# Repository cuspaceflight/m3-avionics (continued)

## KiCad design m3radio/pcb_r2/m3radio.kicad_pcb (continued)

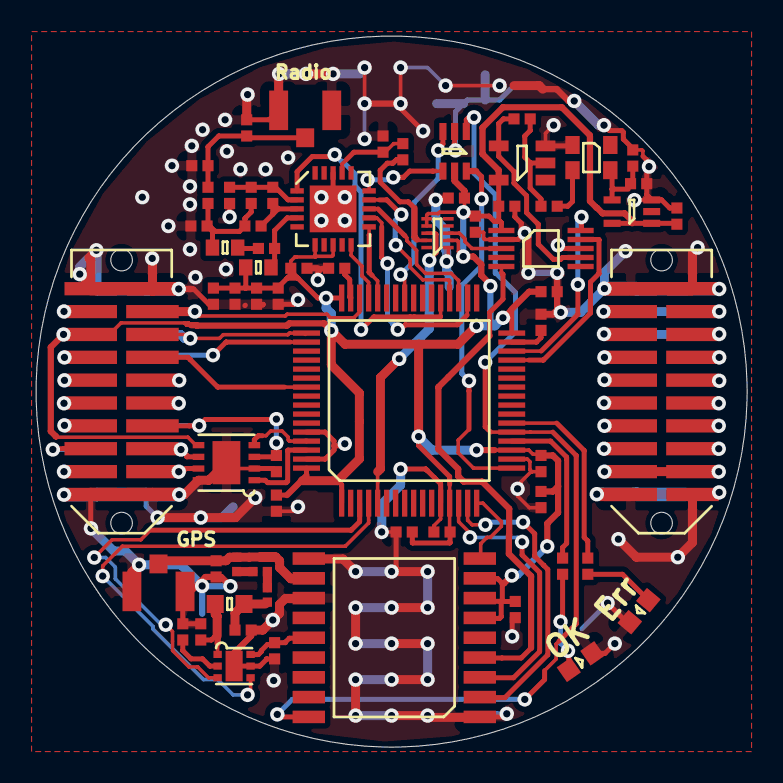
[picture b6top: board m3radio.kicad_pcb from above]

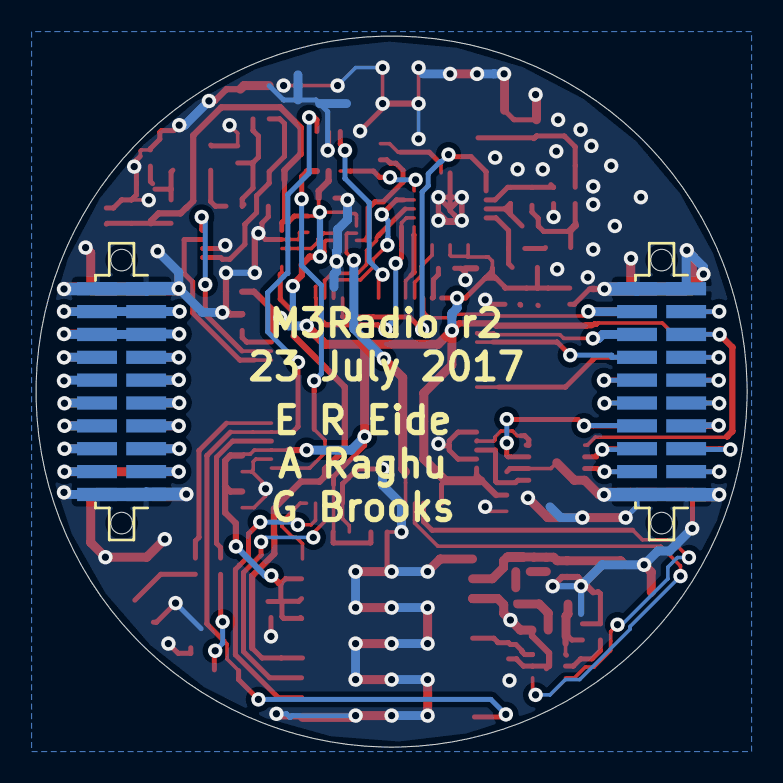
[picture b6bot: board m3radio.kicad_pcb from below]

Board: 2 copper layers, 39.5 x 39.5 mm, 66 parts (2 on the bottom side), 78 nets.

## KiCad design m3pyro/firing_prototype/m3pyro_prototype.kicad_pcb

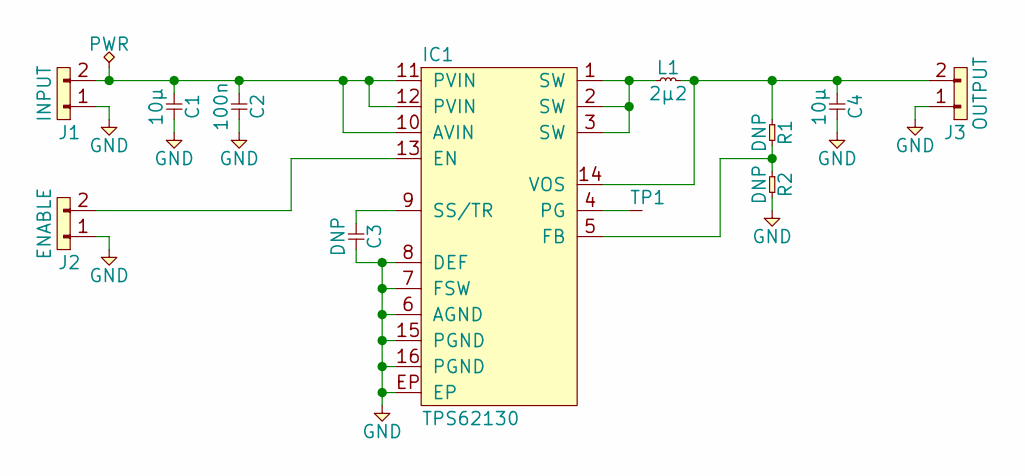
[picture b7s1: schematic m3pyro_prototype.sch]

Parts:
C1, C4: 10µ; 0603
C2: 100n; 0603
C3: DNP; 0603
IC1: TPS62130; QFN-16-EP-TI; Farnell 2361246
J1: INPUT; SIL-254P-02
J2: ENABLE; SIL-254P-02
J3: OUTPUT; SIL-254P-02
L1: 2µ2; XFL4020; Farnell 2289216
R1, R2: DNP; 0603
TP1: TESTPAD

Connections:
GND: C1.2, C2.2, C3.2, C4.2, IC1.6 (AGND), IC1.7 (FSW), IC1.8 (DEF), IC1.15 (PGND), IC1.16 (PGND), IC1.EP, J1.1, J2.1, J3.1, R2.2
unnamed: C1.1, C2.1, IC1.10 (AVIN), IC1.11 (PVIN), IC1.12 (PVIN), J1.2
unnamed: C3.1, IC1.9 (SS/TR)
unnamed: C4.1, IC1.14 (VOS), J3.2, L1.2, R1.1
unnamed: IC1.1 (SW), IC1.2 (SW), IC1.3 (SW), L1.1
unnamed: IC1.4 (PG), TP1.1
unnamed: IC1.5 (FB), R1.2, R2.1
unnamed: IC1.13 (EN), J2.2

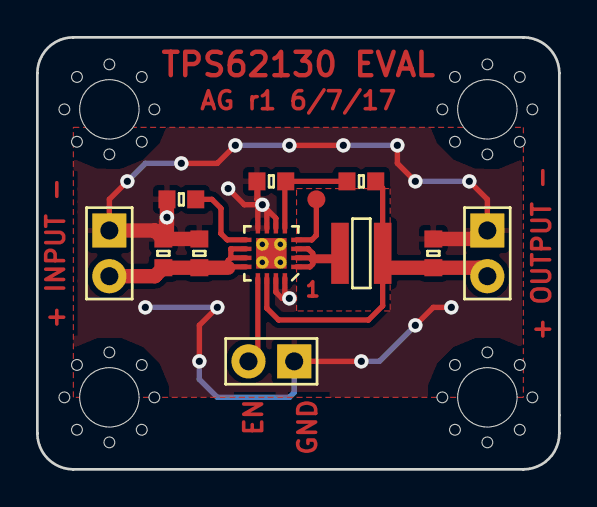
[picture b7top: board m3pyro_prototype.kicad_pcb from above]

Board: 2 copper layers, 29.0 x 24.0 mm, 12 parts (0 on the bottom side), 8 nets.

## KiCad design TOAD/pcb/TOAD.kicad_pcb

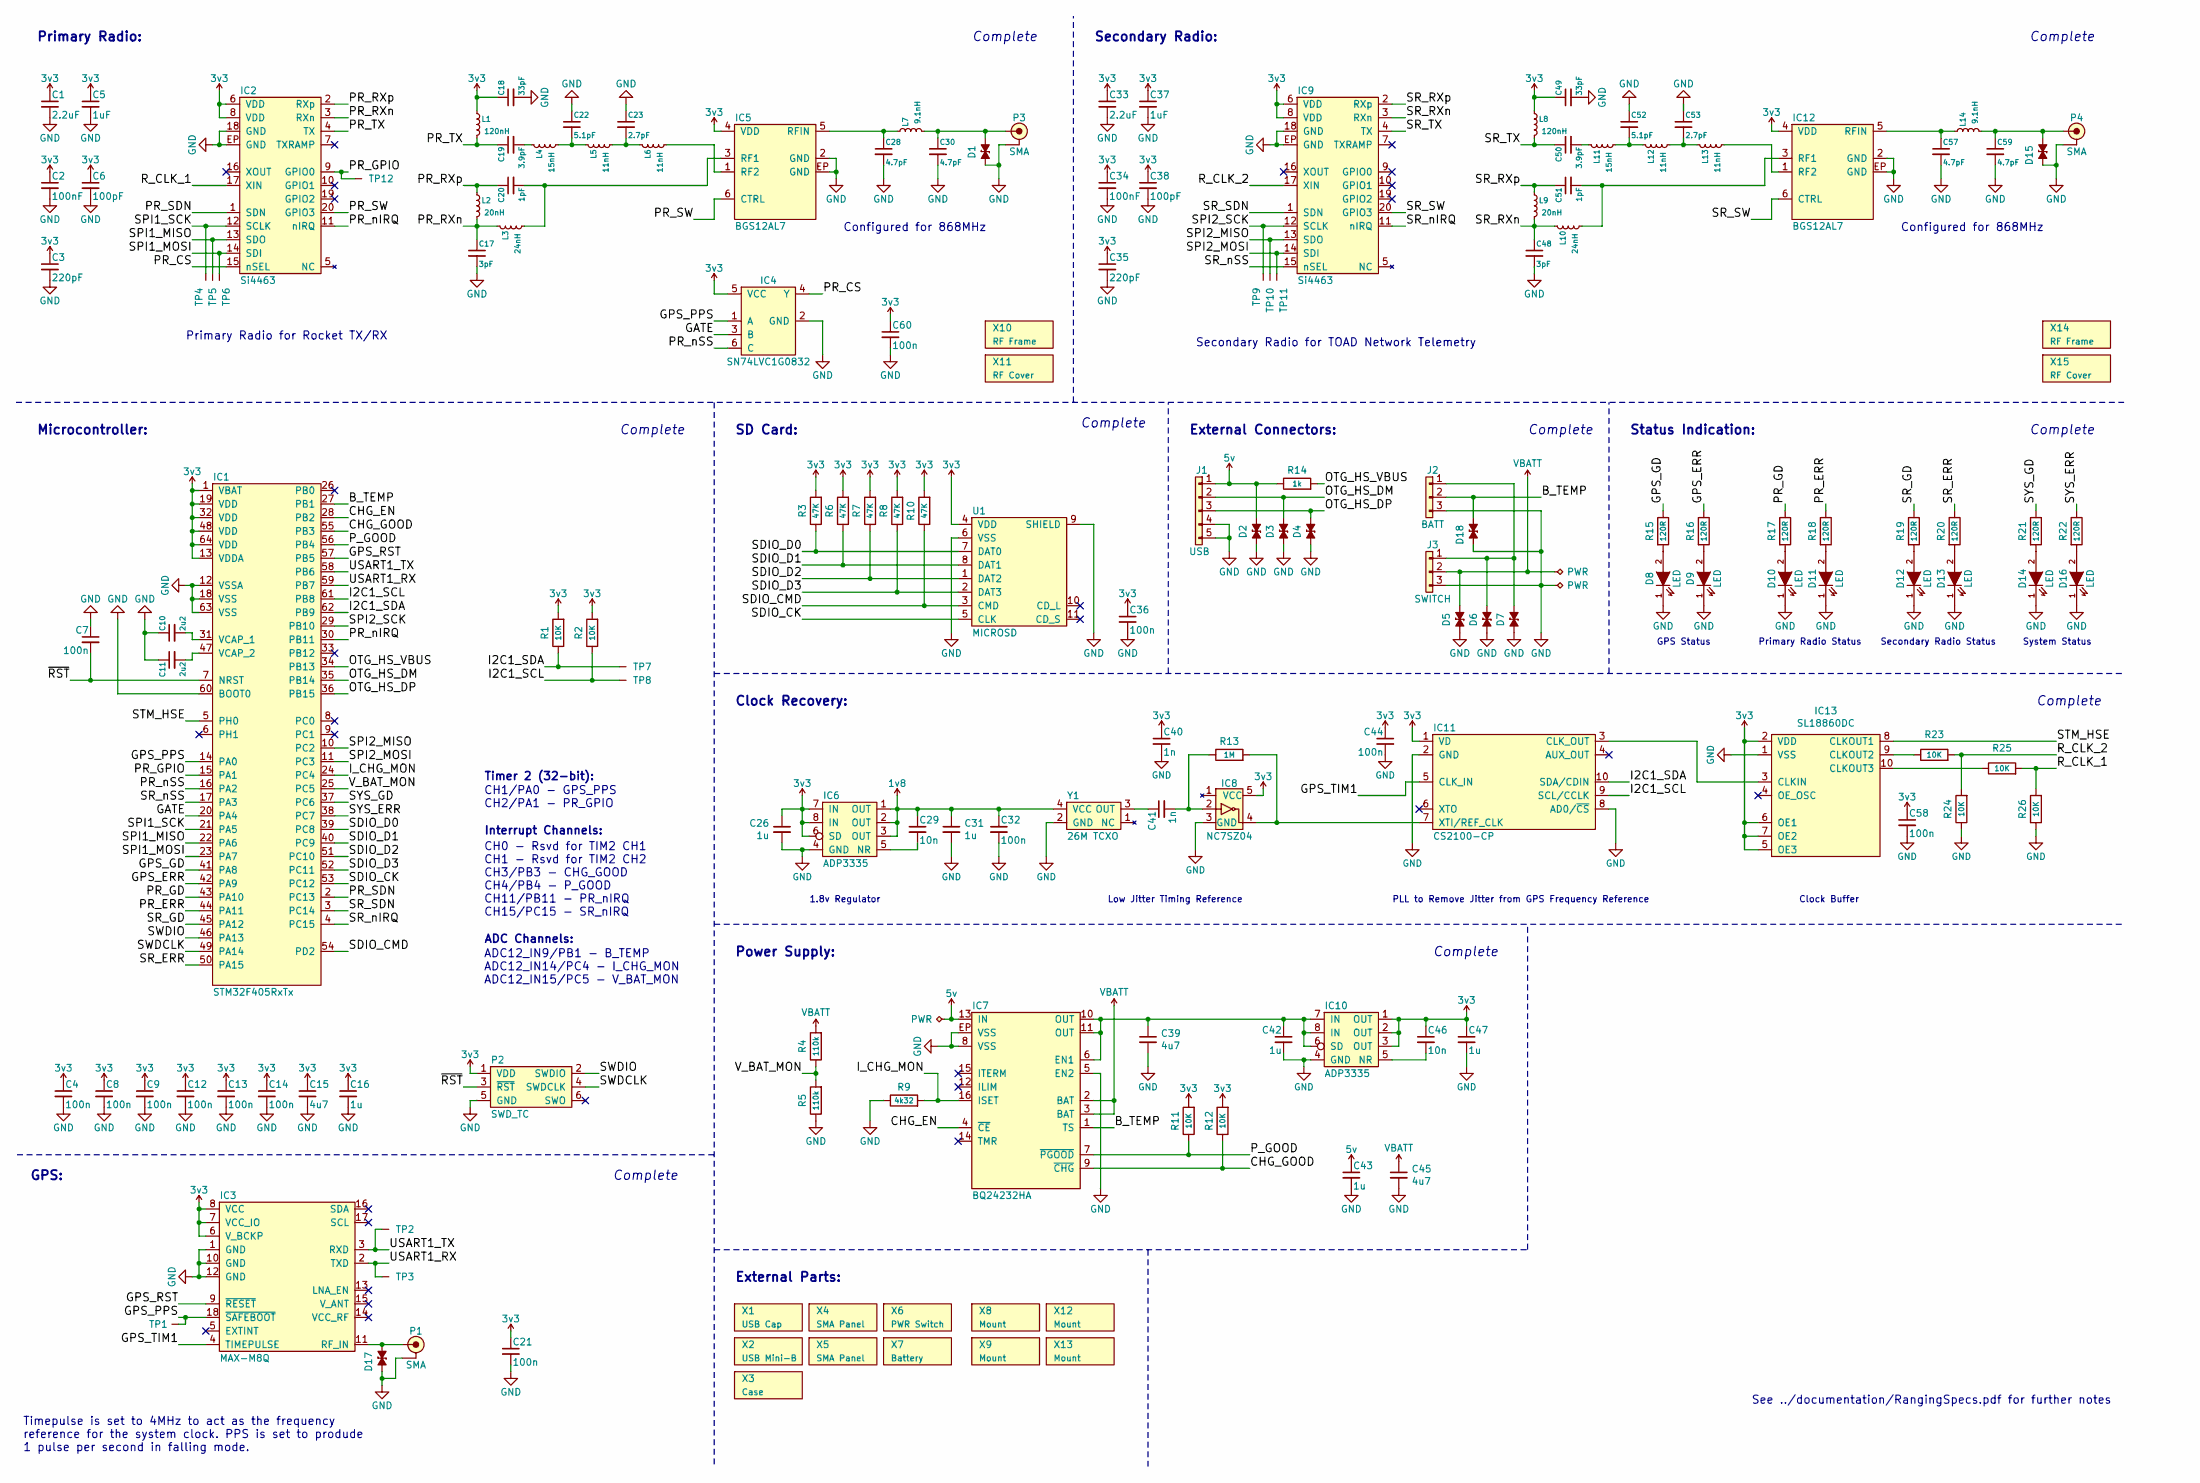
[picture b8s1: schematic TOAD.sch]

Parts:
C1, C33: 2.2uF; 0603-L; Farnell 2346896
C2, C34: 100nF; 0402; Farnell 1828860
C3, C35: 220pF; 0402; Farnell 2496800
C4, C7, C8, C9, C12, C13, C14, C60: 100n; 0402; Farnell 9402047
C5, C37: 1uF; 0603-L; Farnell 2112849
C6, C38: 100pF; 0402; Farnell 2496792
C10, C11: 2u2; 0603-L; Farnell 1797012
C15: 4u7; 0603; Farnell 2496930
C16, C26, C31, C42, C43, C47: 1u; 0603-L; Farnell 1865556
C17, C48: 3pF; 0402; Farnell 2524984
C18, C49: 33pF; 0402; Farnell 2434643
C19, C50: 3.9pF; 0402; Farnell 2672775
C20, C51: 1pF; 0402; Farnell 2133992
C21, C32, C36, C44, C58: 100n; 0603-L; Farnell 2496834
C22, C52: 5.1pF; 0402; Farnell 2688498
C23, C53: 2.7pF; 0402; Farnell 2672771
C28, C30, C57, C59: 4.7pF; 0402; Farnell 2332509
C29, C46: 10n; 0603-L; Farnell 2496825
C39, C45: 4u7; 0603-L; Farnell 2496930
C40, C41: 1n; 0603-L; Farnell 2496882
D1, D2, D3, D4, D5, D6, D7, D15, D17, D18: ESD_DIODE; 0402-L; Farnell 2368169
D8, D10, D12, D14: LED; 0603-LED; Farnell 2290328
D9, D11, D13, D16: LED; 0603-LED; Farnell 2290329
IC1: STM32F405RxTx; LQFP-64; Farnell 2064363
IC2, IC9: Si4463; QFN-20-EP-SI; Farnell 2462637
IC3: MAX-M8Q
IC4: SN74LVC1G0832; SC-70-6; Farnell 2406965
IC5, IC12: BGS12AL7; TSLP7-4; Farnell 2480594
IC6: ADP3335; MSOP-8; Farnell 2376932
IC7: BQ24232HA; QFN-16-EP-TI; Farnell 2576286
IC8: NC7SZ04; SOT-23-5; Farnell 1417667
IC10: ADP3335; MSOP-8; Farnell 2067775
IC11: CS2100-CP; MSOP-10; Mouser 777-CS2100CP-CZZ
IC13: SL18860DC; DFN-10-SL18860DC; Mouser 634-SL18860DC
J1: USB; SIL-254P-05
J2: BATT; S03B-PASK-2; Farnell 1830748
J3: SWITCH; S03B-PASK-2; Farnell 1830748
L1, L8: 120nH; 0402; Farnell 2285871
L2, L9: 20nH; 0402; Farnell 1748728
L3, L10: 24nH; 0402; Farnell 2470344
L4, L11: 15nH; 0402; Farnell 1762621
L5, L6, L12, L13: 11nH; 0402; Farnell 2116067
L7, L14: 9.1nH; 0402; Farnell 1762616
P1: SMA; SMA-EDGE
P2: SWD_TC; TC2030-NL
P3, P4: SMA; SMA-EDGE; Farnell 1608592
R1, R2, R11, R12: 10K; 0603-L; Farnell 9238603
R3, R6, R7, R8, R10: 47K; 0603-L; Farnell 9238689
R4, R5: 110k; 0603-L; Farnell 2502402
R9: 4k32; 0603-L; Farnell 2670808
R13: 1M; 0603-L; Farnell 1469746
R14: 1k; 0603-L; Farnell 2309108
R15, R16, R17, R18, R19, R20, R21, R22: 120R; 0603-L; Farnell 9238379
R23, R24, R25, R26: 10K; 0402; Farnell 2379805
TP1, TP2, TP3, TP4, TP5, TP6, TP7, TP8, TP9, TP10, TP11, TP12: TESTPAD
U1: MICROSD; MICROSD_MOLEX_503398-1892; Farnell 2358234
X1: USB Cap
X2: USB Mini-B
X3: Case
X4, X5: SMA Panel; Farnell 2096227
X6: PWR Switch
X7: Battery; Farnell 2401856
X8, X9, X12, X13: Mount; M3_MOUNT
X10, X14: RF Frame; BMI-S-201-F; Farnell 2497715
X11, X15: RF Cover; Farnell 2497714
Y1: 26M TCXO; XTAL-25x20; Farnell 2405785

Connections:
1v8: C29.1, C31.1, C32.1, IC6.1 (OUT), IC6.2 (OUT), IC6.3 (OUT), Y1.4 (VCC)
3v3: C1.1, C2.1, C3.1, C4.1, C5.1, C6.1, C8.1, C9.1, C12.1, C13.1, C14.1, C15.1, C16.1, C18.1, C21.1, C26.1, C33.1, C34.1, C35.1, C36.1, C37.1, C38.1, C40.1, C44.1, C46.1, C47.1, C49.1, C58.1, C60.1, IC1.1 (VBAT), IC1.13 (VDDA), IC1.19 (VDD), IC1.32 (VDD), IC1.48 (VDD), IC1.64 (VDD), IC2.6 (VDD), IC2.8 (VDD), IC3.6 (V_BCKP), IC3.7 (VCC_IO), IC3.8 (VCC), IC4.5 (VCC), IC5.4 (VDD), IC6.6 (SD), IC6.7 (IN), IC6.8 (IN), IC8.5 (VCC), IC9.6 (VDD), IC9.8 (VDD), IC10.1 (OUT), IC10.2 (OUT), IC10.3 (OUT), IC11.1 (VD), IC12.4 (VDD), IC13.2 (VDD), IC13.5 (OE3), IC13.6 (OE1), IC13.7 (OE2), L1.1, L8.1, P2.1 (VDD), R1.2, R2.2, R3.2, R6.2, R7.2, R8.2, R10.2, R11.2, R12.2, U1.4 (VDD)
5v: C43.1, D2.1, IC7.13 (IN), J1.1, R14.1
/B_TEMP: D18.1, IC1.27 (PB1), IC7.1 (TS), J2.2
/CHG_EN: IC1.28 (PB2), IC7.4 (~CE)
/CHG_GOOD: IC1.55 (PB3), IC7.9 (~CHG), R12.1
/GATE: IC1.20 (PA4), IC4.3 (B)
/GPS_ERR: IC1.42 (PA9), R16.1
/GPS_GD: IC1.41 (PA8), R15.1
/GPS_PPS: IC1.14 (PA0), IC3.18 (~SAFEBOOT), IC4.1 (A), TP1.1
/GPS_RST: IC1.57 (PB5), IC3.9 (~RESET)
/GPS_TIM1: IC3.4 (TIMEPULSE), IC11.5 (CLK_IN)
/I2C1_SCL: IC1.61 (PB8), IC11.9 (SCL/CCLK), R2.1, TP8.1
/I2C1_SDA: IC1.62 (PB9), IC11.10 (SDA/CDIN), R1.1, TP7.1
/I_CHG_MON: IC1.24 (PC4), IC7.16 (ISET), R9.2
/OTG_HS_DM: D3.1, IC1.35 (PB14), J1.2
/OTG_HS_DP: D4.1, IC1.36 (PB15), J1.3
/OTG_HS_VBUS: IC1.34 (PB13), R14.2
/PR_CS: IC2.15 (nSEL), IC4.4 (Y)
/PR_ERR: IC1.44 (PA11), R18.1
/PR_GD: IC1.43 (PA10), R17.1
/PR_GPIO: IC1.15 (PA1), IC2.9 (GPIO0), TP12.1
/PR_RXn: C17.1, IC2.3 (RXn), L2.2, L3.1
/PR_RXp: C20.1, IC2.2 (RXp), L2.1
/PR_SDN: IC1.2 (PC13), IC2.1 (SDN)
/PR_SW: IC2.20 (GPIO3), IC5.6 (CTRL)
/PR_TX: C19.1, IC2.4 (TX), L1.2
/PR_nIRQ: IC1.30 (PB11), IC2.11 (nIRQ)
/PR_nSS: IC1.16 (PA2), IC4.6 (C)
/P_GOOD: IC1.56 (PB4), IC7.7 (~PGOOD), R11.1
/R_CLK_1: IC2.17 (XIN), R25.2, R26.2
/R_CLK_2: IC9.17 (XIN), R23.2, R24.2
/SDIO_CK: IC1.53 (PC12), U1.5 (CLK)
/SDIO_CMD: IC1.54 (PD2), R10.1, U1.3 (CMD)
/SDIO_D0: IC1.39 (PC8), R3.1, U1.7 (DAT0)
/SDIO_D1: IC1.40 (PC9), R6.1, U1.8 (DAT1)
/SDIO_D2: IC1.51 (PC10), R7.1, U1.1 (DAT2)
/SDIO_D3: IC1.52 (PC11), R8.1, U1.2 (DAT3)
/SPI1_MISO: IC1.22 (PA6), IC2.13 (SDO), TP5.1
/SPI1_MOSI: IC1.23 (PA7), IC2.14 (SDI), TP6.1
/SPI1_SCK: IC1.21 (PA5), IC2.12 (SCLK), TP4.1
/SPI2_MISO: IC1.10 (PC2), IC9.13 (SDO), TP10.1
/SPI2_MOSI: IC1.11 (PC3), IC9.14 (SDI), TP11.1
/SPI2_SCK: IC1.29 (PB10), IC9.12 (SCLK), TP9.1
/SR_ERR: IC1.50 (PA15), R20.1
/SR_GD: IC1.45 (PA12), R19.1
/SR_RXn: C48.1, IC9.3 (RXn), L9.2, L10.1
/SR_RXp: C51.1, IC9.2 (RXp), L9.1
/SR_SDN: IC1.3 (PC14), IC9.1 (SDN)
/SR_SW: IC9.20 (GPIO3), IC12.6 (CTRL)
/SR_TX: C50.1, IC9.4 (TX), L8.2
/SR_nIRQ: IC1.4 (PC15), IC9.11 (nIRQ)
/SR_nSS: IC1.17 (PA3), IC9.15 (nSEL)
/STM_HSE: IC1.5 (PH0), IC13.8 (CLKOUT1)
/SWDCLK: IC1.49 (PA14), P2.4 (SWDCLK)
/SWDIO: IC1.46 (PA13), P2.2 (SWDIO)
/SYS_ERR: IC1.38 (PC7), R22.1
/SYS_GD: IC1.37 (PC6), R21.1
/USART1_RX: IC1.59 (PB7), IC3.2 (TXD), TP3.1
/USART1_TX: IC1.58 (PB6), IC3.3 (RXD), TP2.1
/V_BAT_MON: IC1.25 (PC5), R4.1, R5.2
/~RST: C7.2, IC1.7 (NRST), P2.3 (~RST)
GND: C1.2, C2.2, C3.2, C4.2, C5.2, C6.2, C7.1, C8.2, C9.2, C10.1, C11.1, C12.2, C13.2, C14.2, C15.2, C16.2, C17.2, C18.2, C21.2, C22.1, C23.1, C26.2, C28.2, C30.2, C31.2, C32.2, C33.2, C34.2, C35.2, C36.2, C37.2, C38.2, C39.2, C40.2, C42.2, C43.2, C44.2, C45.2, C47.2, C48.2, C49.2, C52.1, C53.1, C57.2, C58.2, C59.2, C60.2, D1.2, D2.2, D3.2, D4.2, D5.2, D6.2, D7.2, D8.1 (K), D9.1 (K), D10.1 (K), D11.1 (K), D12.1 (K), D13.1 (K), D14.1 (K), D15.2, D16.1 (K), D17.2, D18.2, IC1.12 (VSSA), IC1.18 (VSS), IC1.60 (BOOT0), IC1.63 (VSS), IC2.18 (GND), IC2.EP (GND), IC3.1 (GND), IC3.10 (GND), IC3.12 (GND), IC4.2 (GND), IC5.2 (GND), IC5.EP (GND), IC6.4 (GND), IC7.5 (EN2), IC7.8 (VSS), IC7.EP (VSS), IC8.3 (GND), IC9.18 (GND), IC9.EP (GND), IC10.4 (GND), IC11.2 (GND), IC11.8 (AD0/~CS), IC12.2 (GND), IC12.EP (GND), IC13.1 (VSS), J1.4, J1.5, J2.3, J3.3, P1.2 (GND), P2.5 (GND), P3.2 (GND), P4.2 (GND), R5.1, R9.1, R24.1, R26.1, U1.6 (VSS), U1.9 (SHIELD), Y1.2 (GND)
unnamed: C10.2, IC1.31 (VCAP_1)
unnamed: C11.2, IC1.47 (VCAP_2)
unnamed: C19.2, L4.1
unnamed: C20.2, IC5.3 (RF1), L3.2
unnamed: C22.2, L4.2, L5.1
unnamed: C23.2, L5.2, L6.1
unnamed: C28.1, IC5.5 (RFIN), L7.1
unnamed: C29.2, IC6.5 (NR)
unnamed: C30.1, D1.1, L7.2, P3.1 (RF)
unnamed: C39.1, C42.1, IC7.6 (EN1), IC7.10 (OUT), IC7.11 (OUT), IC10.6 (SD), IC10.7 (IN), IC10.8 (IN)
unnamed: C41.1, Y1.3 (OUT)
unnamed: C41.2, IC8.2, R13.1
unnamed: C46.2, IC10.5 (NR)
unnamed: C50.2, L11.1
unnamed: C51.2, IC12.3 (RF1), L10.2
unnamed: C52.2, L11.2, L12.1
unnamed: C53.2, L12.2, L13.1
unnamed: C57.1, IC12.5 (RFIN), L14.1
unnamed: C59.1, D15.1, L14.2, P4.1 (RF)
unnamed: D6.1, D7.1, J2.1, J3.1
unnamed: D8.2 (A), R15.2
unnamed: D9.2 (A), R16.2
unnamed: D10.2 (A), R17.2
unnamed: D11.2 (A), R18.2
unnamed: D12.2 (A), R19.2
unnamed: D13.2 (A), R20.2
unnamed: D14.2 (A), R21.2
unnamed: D16.2 (A), R22.2
unnamed: D17.1, IC3.11 (RF_IN), P1.1 (RF)
unnamed: IC5.1 (RF2), L6.2
unnamed: IC11.3 (CLK_OUT), IC13.3 (CLKIN)
unnamed: IC8.4, IC11.7 (XTI/REF_CLK), R13.2
unnamed: IC12.1 (RF2), L13.2
unnamed: IC13.9 (CLKOUT2), R23.1
unnamed: IC13.10 (CLKOUT3), R25.1
VBATT: C45.1, D5.1, IC7.2 (BAT), IC7.3 (BAT), J3.2, R4.2

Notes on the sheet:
Configured for 868MHz
Primary Radio:
Microcontroller:
Complete
Secondary Radio:
GPS:
SD Card:
External Connectors:
Timepulse is set to 4MHz to act as the frequency reference for the system clock. PPS is set to produde 1 pulse per second in falling mode.
Clock Recovery:
Power Supply:
1.8v Regulator
Low Jitter Timing Reference
PLL to Remove Jitter from GPS Frequency Reference
Status Indication:
GPS Status
Primary Radio Status
Secondary Radio Status
System Status
Clock Buffer
Primary Radio for Rocket TX/RX
Secondary Radio for TOAD Network Telemetry
CH1/PA0 - GPS_PPS CH2/PA1 - PR_GPIO
Timer 2 (32-bit):
CH0 - Rsvd for TIM2 CH1 CH1 - Rsvd for TIM2 CH2 CH3/PB3 - CHG_GOOD CH4/PB4 - P_GOOD CH11/PB11 - PR_nIRQ CH15/PC15 - SR_nIRQ
Interrupt Channels:
ADC Channels:
ADC12_IN9/PB1 - B_TEMP ADC12_IN14/PC4 - I_CHG_MON ADC12_IN15/PC5 - V_BAT_MON
External Parts:
See ../documentation/RangingSpecs.pdf for further notes

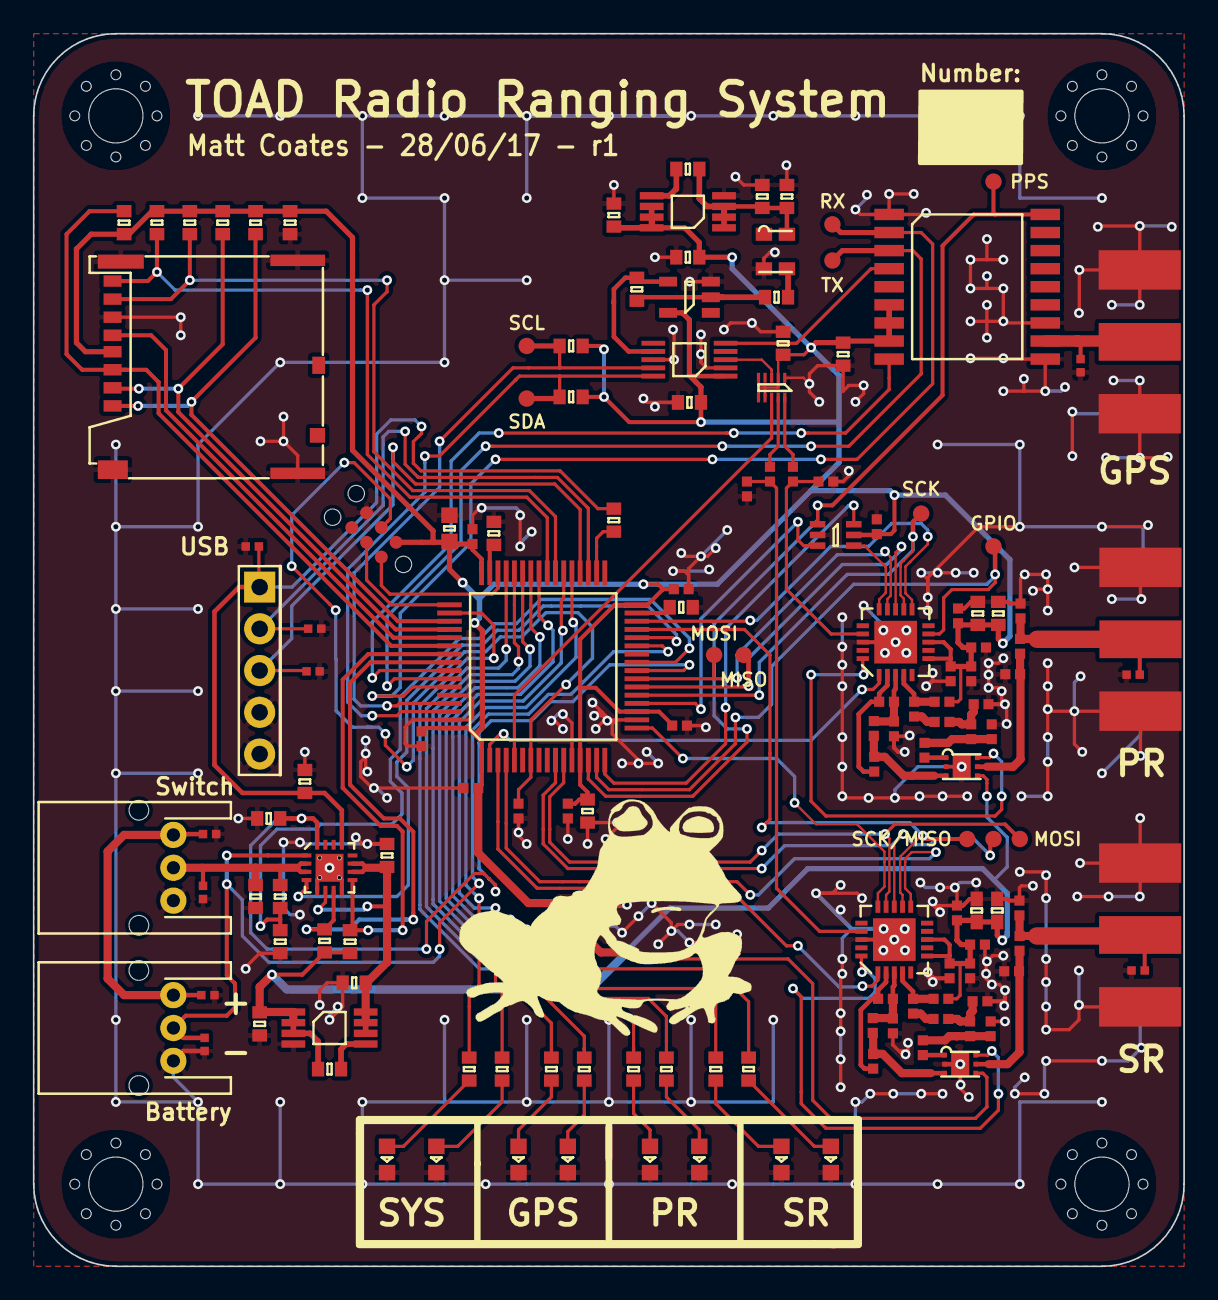
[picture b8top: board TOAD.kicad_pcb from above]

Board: 2 copper layers, 70.0 x 75.0 mm, 152 parts (0 on the bottom side), 99 nets.

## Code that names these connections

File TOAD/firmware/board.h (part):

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/*
 *  GPIOA setup:
 *
 * PA0  - GPS_PPS                      (af1).
 * PA1  - PR_GPIO                      (af1).
 * PA2  - PR_NSS                       (output, pushpull, starthigh, pullup).
 * PA3  - SR_NSS                       (output, pushpull, starthigh, pullup).
 * PA4  - GATE                         (output, pushpull, startlow, pulldown).
 * PA5  - SPI1_SCK                     (af5).
 * PA6  - SPI1_MISO                    (af5).
 * PA7  - SPI1_MOSI                    (af5).
 * PA8  - GPS_GD                       (output, pushpull, startlow).
 * PA9  - GPS_ERR                      (output, pushpull, startlow).
 * PA10 - PR_GD                        (output, pushpull, startlow).
 * PA11 - PR_ERR                       (output, pushpull, startlow).
 * PA12 - SR_GD                        (output, pushpull, startlow).
 * PA13 - SWDIO                        (af0).
 * PA14 - SWCLK                        (pulldown, af0).
 * PA15 - SR_ERR                       (output, pushpull, startlow).
*/
#define VAL_GPIOA_MODER                (PIN_MODE_ALTERNATE(GPIOA_GPS_PPS) | \
                                        PIN_MODE_ALTERNATE(GPIOA_PR_GPIO) | \
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 *  GPIOB setup:
 *
 * PB0  - PIN0                         (unused).
 * PB1  - B_TEMP                       (analog, floating).
 * PB2  - CHG_EN                       (output, pushpull, startlow, pulldown).
 * PB3  - CHG_GOOD                     (input, pushpull).
 * PB4  - POWER_GOOD                   (input, pushpull).
 * PB5  - GPS_RST                      (output, pushpull, starthigh, pullup).
 * PB6  - UART_TX                      (af7).
 * PB7  - UART_RX                      (af7).
 * PB8  - I2C_SCL                      (af4, opendrain).
 * PB9  - I2C_SDA                      (af4, opendrain).
 * PB10 - SPI2_SCK                     (af5).
 * PB11 - PR_NIRQ                      (input, pushpull, pullup).
 * PB12 - PIN12                        (unused).
 * PB13 - OTG_VBUS                     (input, pulldown).
 * PB14 - OTG_DM                       (af12).
 * PB15 - OTG_DP                       (af12).
*/
#define VAL_GPIOB_MODER                (PIN_MODE_INPUT(GPIOB_PIN0) | \
                                        PIN_MODE_ANALOG(GPIOB_B_TEMP) | \
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/*
 *  GPIOC setup:
 *
 * PC0  - SR_SW                        (output, pushpull).
 * PC1  - PR_SW                        (output, pushpull).
 * PC2  - SPI2_MISO                    (af5).
 * PC3  - SPI2_MOSI                    (af5).
 * PC4  - I_CHG_MON                    (analog, floating).
 * PC5  - V_BAT_MON                    (analog, floating).
 * PC6  - SYS_GD                       (output, pushpull, startlow).
 * PC7  - SYS_ERR                      (output, pushpull, startlow).
 * PC8  - SDIO_DO                      (af12).
 * PC9  - SDIO_D1                      (af12).
 * PC10 - SDIO_D2                      (af12).
 * PC11 - SDIO_D3                      (af12).
 * PC12 - SDIO_CK                      (af12).
 * PC13 - PR_SDN                       (output, pushpull).
 * PC14 - SR_SDN                       (output, pushpull).
 * PC15 - SR_NIRQ                      (input, pushpull, pullup).
*/
#define VAL_GPIOC_MODER                (PIN_MODE_OUTPUT(GPIOC_SR_SW) | \
                                        PIN_MODE_OUTPUT(GPIOC_PR_SW) | \
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 *
 * PD0  - PIN0                         (unused).
 * PD1  - PIN1                         (unused).
 * PD2  - SDIO_CMD                     (af12).
 * PD3  - PIN3                         (unused).
 * PD4  - PIN4                         (unused).
 * PD5  - PIN5                         (unused).
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/*
 *  GPIOH setup:
 *
 * PH0  - PIN0                         (unused).
 * PH1  - PIN1                         (unused).
 * PH2  - PIN2                         (unused).
 * PH3  - PIN3                         (unused).
 * PH4  - PIN4                         (unused).
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
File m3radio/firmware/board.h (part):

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/*
 *  GPIOA setup:
 *
 * PA0  - GPS_RX                       (af8).
 * PA1  - GPS_TX                       (af8).
 * PA2  - GPS_RESET_N                  (output, pushpull, starthigh, pullup).
 * PA3  - RADIO_CS                     (output, pushpull, starthigh, pullup).
 * PA4  - LED_RED                      (output, startlow).
 * PA5  - GPS_PPS                      (input, floating).
 * PA6  - LED_GRN                      (output, startlow).
 * PA7  - PIN7                         (unused).
 * PA8  - RADIO_GATE                   (output, pushpull, startlow, pulldown).
 * PA9  - PIN9                         (unused).
 * PA10 - PIN10                        (unused).
 * PA11 - RADIO_IRQ_N                  (input, pushpull, pullup).
 * PA12 - RADIO_GPIO1                  (input).
 * PA13 - JTMS                         (af0, pulldown).
 * PA14 - JTCK                         (af0, pulldown).
 * PA15 - JTDI                         (af0, pullup).
*/
#define VAL_GPIOA_MODER                (PIN_MODE_ALTERNATE(GPIOA_GPS_RX) | \
                                        PIN_MODE_ALTERNATE(GPIOA_GPS_TX) | \
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 *  GPIOB setup:
 *
 * PB0  - PIN0                         (unused).
 * PB1  - PIN1                         (unused).
 * PB2  - PIN2                         (unused).
 * PB3  - JTDO                         (af0).
 * PB4  - NJTRST                       (af0, pullup).
 * PB5  - PIN5                         (unused).
 * PB6  - PIN6                         (unused).
 * PB7  - PIN7                         (unused).
 * PB8  - CAN_RX                       (af9).
 * PB9  - CAN_TX                       (af9).
 * PB10 - PLL_SCL                      (af4, pullup, opendrain).
 * PB11 - PLL_SDA                      (af4, pullup, opendrain).
 * PB12 - PIN12                        (unused).
 * PB13 - RADIO_SCLK                   (af5).
 * PB14 - RADIO_SDO                    (af5).
 * PB15 - RADIO_SDI                    (af5).
*/
#define VAL_GPIOB_MODER                (PIN_MODE_INPUT(GPIOB_PIN0) | \
                                        PIN_MODE_INPUT(GPIOB_PIN1) | \
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 *
 * PC0  - PIN0                         (unused).
 * PC1  - PIN1                         (unused).
 * PC2  - PIN2                         (unused).
 * PC3  - PIN3                         (unused).
 * PC4  - PIN4                         (unused).
 * PC5  - PIN5                         (unused).
 * PC6  - RADIO_SDN                    (output, starthigh, pushpull).
 * PC7  - PIN7                         (unused).
 * PC8  - PIN8                         (unused).
 * PC9  - PIN9                         (unused).
 * PC10 - PIN10                        (unused).
 * PC11 - PIN11                        (unused).
 * PC12 - PIN12                        (unused).
 * PC13 - PIN13                        (unused).
 * PC14 - ANT_FLAG_N                   ().
 * PC15 - ANT_EN                       (output, pushpull, startlow).
*/
#define VAL_GPIOC_MODER                (PIN_MODE_INPUT(GPIOC_PIN0) | \
                                        PIN_MODE_INPUT(GPIOC_PIN1) | \
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 *
 * PD0  - PIN0                         (unused).
 * PD1  - PIN1                         (unused).
 * PD2  - PIN2                         (unused).
 * PD3  - PIN3                         (unused).
 * PD4  - PIN4                         (unused).
 * PD5  - PIN5                         (unused).
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/*
 *  GPIOH setup:
 *
 * PH0  - PIN0                         (unused).
 * PH1  - PIN1                         (unused).
 * PH2  - PIN2                         (unused).
 * PH3  - PIN3                         (unused).
 * PH4  - PIN4                         (unused).
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
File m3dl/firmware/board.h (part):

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/*
 *  GPIOA setup:
 *
 * PA0  - STRAIN5                      (analog, floating).
 * PA1  - STRAIN6                      (analog, floating).
 * PA2  - PRESSURE_TX                  (af7).
 * PA3  - PRESSURE_RX                  (af7).
 * PA4  - PIN4                         (unused).
 * PA5  - SPI1_SCK                     (af5).
 * PA6  - SPI1_MISO                    (af5).
 * PA7  - SPI1_MOSI                    (af5).
 * PA8  - SPI1_CS                      (output, pushpull).
 * PA9  - PIN9                         (unused).
 * PA10 - PIN10                        (unused).
 * PA11 - PIN11                        (unused).
 * PA12 - PIN12                        (unused).
 * PA13 - JTMS                         (af0, pulldown).
 * PA14 - JTCK                         (af0, pulldown).
 * PA15 - JTDI                         (af0, pullup).
*/
#define VAL_GPIOA_MODER                (PIN_MODE_ANALOG(GPIOA_STRAIN5) | \
                                        PIN_MODE_ANALOG(GPIOA_STRAIN6) | \
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 *  GPIOB setup:
 *
 * PB0  - PIN0                         (unused).
 * PB1  - PIN1                         (unused).
 * PB2  - PIN2                         (unused).
 * PB3  - JTDO                         (af0).
 * PB4  - NJTRST                       (af0, pullup).
 * PB5  - PIN5                         (unused).
 * PB6  - PIN6                         (unused).
 * PB7  - TEMP_INT                     (input, pulldown).
 * PB8  - CAN_RX                       (af9).
 * PB9  - CAN_TX                       (af9).
 * PB10 - PIN10                        (unused).
 * PB11 - PIN11                        (unused).
 * PB12 - LED1_GREEN                   (output, pushpull, startlow).
 * PB13 - OTG_HS_VBUS                  (input, pulldown).
 * PB14 - OTG_HS_DM                    (af12).
 * PB15 - OTG_HS_DP                    (af12).
*/
#define VAL_GPIOB_MODER                (PIN_MODE_INPUT(GPIOB_PIN0) | \
                                        PIN_MODE_INPUT(GPIOB_PIN1) | \
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 *
 * PC0  - STRAIN1                      (analog, floating).
 * PC1  - STRAIN2                      (analog, floating).
 * PC2  - STRAIN3                      (analog, floating).
 * PC3  - STRAIN4                      (analog, floating).
 * PC4  - PIN4                         (unused).
 * PC5  - PIN5                         (unused).
 * PC6  - PIN6                         (unused).
 * PC7  - LED2_RED                     (output, pushpull, startlow).
 * PC8  - SDIO_DO                      (af12).
 * PC9  - SDIO_D1                      (af12).
 * PC10 - SDIO_D2                      (af12).
 * PC11 - SDIO_D3                      (af12).
 * PC12 - SDIO_CK                      (af12).
 * PC13 - PIN13                        (unused).
 * PC14 - PIN14                        (unused).
 * PC15 - PIN15                        (unused).
*/
#define VAL_GPIOC_MODER                (PIN_MODE_ANALOG(GPIOC_STRAIN1) | \
                                        PIN_MODE_ANALOG(GPIOC_STRAIN2) | \
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 *
 * PD0  - PIN0                         (unused).
 * PD1  - PIN1                         (unused).
 * PD2  - SDIO_CMD                     (af12).
 * PD3  - PIN3                         (unused).
 * PD4  - PIN4                         (unused).
 * PD5  - PIN5                         (unused).
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/*
 *  GPIOH setup:
 *
 * PH0  - PIN0                         (unused).
 * PH1  - PIN1                         (unused).
 * PH2  - PIN2                         (unused).
 * PH3  - PIN3                         (unused).
 * PH4  - PIN4                         (unused).
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
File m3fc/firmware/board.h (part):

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/*
 *  GPIOA setup:
 *
 * PA0  - BEEPER                       (af2, startlow).
 * PA1  - LED_RED                      (output, startlow).
 * PA2  - LED_YLW                      (output, startlow).
 * PA3  - LED_GRN                      (output, startlow).
 * PA4  - PIN4                         (unused).
 * PA5  - BARO_SCLK                    (af5).
 * PA6  - BARO_SDO                     (af5).
 * PA7  - BARO_SDI                     (af5).
 * PA8  - PIN8                         (unused).
 * PA9  - PIN9                         (unused).
 * PA10 - PIN10                        (unused).
 * PA11 - ACCEL_INT                    ().
 * PA12 - ACCEL_CS                     (output).
 * PA13 - JTMS                         (af0, pulldown).
 * PA14 - JTCK                         (af0, pulldown).
 * PA15 - JTDI                         (af0, pullup).
*/
#define VAL_GPIOA_MODER                (PIN_MODE_ALTERNATE(GPIOA_BEEPER) | \
                                        PIN_MODE_OUTPUT(GPIOA_LED_RED) | \
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 *  GPIOB setup:
 *
 * PB0  - PIN0                         (unused).
 * PB1  - PIN1                         (unused).
 * PB2  - PIN2                         (unused).
 * PB3  - JTDO                         (af0).
 * PB4  - NJTRST                       (af0, pullup).
 * PB5  - PIN5                         (unused).
 * PB6  - PIN6                         (unused).
 * PB7  - PIN7                         (unused).
 * PB8  - CAN_RX                       (af9).
 * PB9  - CAN_TX                       (af9).
 * PB10 - PIN10                        (unused).
 * PB11 - PIN11                        (unused).
 * PB12 - PIN12                        (unused).
 * PB13 - ACCEL_SCLK                   (af5).
 * PB14 - ACCEL_SDO                    (af5).
 * PB15 - ACCEL_SDI                    (af5).
*/
#define VAL_GPIOB_MODER                (PIN_MODE_INPUT(GPIOB_PIN0) | \
                                        PIN_MODE_INPUT(GPIOB_PIN1) | \
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 *
 * PC0  - PIN0                         (unused).
 * PC1  - PIN1                         (unused).
 * PC2  - PIN2                         (unused).
 * PC3  - PIN3                         (unused).
 * PC4  - BARO_CS                      (output).
 * PC5  - PIN5                         (unused).
 * PC6  - PIN6                         (unused).
 * PC7  - PIN7                         (unused).
 * PC8  - PIN8                         (unused).
 * PC9  - PIN9                         (unused).
 * PC10 - PIN10                        (unused).
 * PC11 - PIN11                        (unused).
 * PC12 - PIN12                        (unused).
 * PC13 - PIN13                        (unused).
 * PC14 - PIN14                        (unused).
 * PC15 - PIN15                        (unused).
*/
#define VAL_GPIOC_MODER                (PIN_MODE_INPUT(GPIOC_PIN0) | \
                                        PIN_MODE_INPUT(GPIOC_PIN1) | \
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 *
 * PD0  - PIN0                         (unused).
 * PD1  - PIN1                         (unused).
 * PD2  - PIN2                         (unused).
 * PD3  - PIN3                         (unused).
 * PD4  - PIN4                         (unused).
 * PD5  - PIN5                         (unused).
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/*
 *  GPIOH setup:
 *
 * PH0  - PIN0                         (unused).
 * PH1  - PIN1                         (unused).
 * PH2  - PIN2                         (unused).
 * PH3  - PIN3                         (unused).
 * PH4  - PIN4                         (unused).
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
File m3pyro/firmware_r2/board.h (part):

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/*
 *  GPIOA setup:
 *
 * PA0  - LED_RED                      (output, startlow, floating).
 * PA1  - LED_YLW                      (output, startlow, floating).
 * PA2  - LED_GRN                      (output, startlow, floating).
 * PA3  - PIN3                         (unused).
 * PA4  - SI_DIV                       (analog, floating).
 * PA5  - BUS_DIV                      (analog, floating).
 * PA6  - CONT                         (analog, floating).
 * PA7  - CONT_EN                      (output, startlow, floating).
 * PA8  - CONT_PASSTHROUGH             (input, floating).
 * PA9  - BUS_DIV_PASSTHROUGH          (input, floating).
 * PA10 - 1A_EN                        (output, startlow, floating).
 * PA11 - SI_DIV_PASSTHROUGH           (input, floating).
 * PA12 - 3A_EN                        (output, startlow, floating).
 * PA13 - JTMS                         (af0, pulldown).
 * PA14 - JTCK                         (af0, pulldown).
 * PA15 - JTDI                         (af0, pullup).
*/
#define VAL_GPIOA_MODER                (PIN_MODE_OUTPUT(GPIOA_LED_RED) | \
                                        PIN_MODE_OUTPUT(GPIOA_LED_YLW) | \
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 *  GPIOB setup:
 *
 * PB0  - PIN0                         (unused).
 * PB1  - PIN1                         (unused).
 * PB2  - PIN2                         (unused).
 * PB3  - JTDO                         (af0).
 * PB4  - NJTRST                       (af0, pullup).
 * PB5  - PIN5                         (unused).
 * PB6  - PIN6                         (unused).
 * PB7  - 3V3_PASSTHROUGH              (input, floating).
 * PB8  - CAN_RX                       (af9).
 * PB9  - CAN_TX                       (af9).
 * PB10 - PIN10                        (unused).
 * PB11 - PIN11                        (unused).
 * PB12 - CH1                          (output, startlow, floating).
 * PB13 - CH5                          (output, startlow, floating).
 * PB14 - PIN14                        (unused).
 * PB15 - CH2                          (output, startlow, floating).
*/
#define VAL_GPIOB_MODER                (PIN_MODE_INPUT(GPIOB_PIN0) | \
                                        PIN_MODE_INPUT(GPIOB_PIN1) | \
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 *
 * PC0  - PIN0                         (unused).
 * PC1  - PIN1                         (unused).
 * PC2  - PIN2                         (unused).
 * PC3  - PIN3                         (unused).
 * PC4  - CH4                          (output, startlow, floating).
 * PC5  - CH8                          (output, startlow, floating).
 * PC6  - CH6                          (output, startlow, floating).
 * PC7  - CH3                          (output, startlow, floating).
 * PC8  - CH7                          (output, startlow, floating).
 * PC9  - CONT_EN_PASSTHROUGH          (input, floating).
 * PC10 - PIN10                        (unused).
 * PC11 - PIN11                        (unused).
 * PC12 - PIN12                        (unused).
 * PC13 - PIN13                        (unused).
 * PC14 - PIN14                        (unused).
 * PC15 - PIN15                        (unused).
*/
#define VAL_GPIOC_MODER                (PIN_MODE_INPUT(GPIOC_PIN0) | \
                                        PIN_MODE_INPUT(GPIOC_PIN1) | \
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 *
 * PD0  - PIN0                         (unused).
 * PD1  - PIN1                         (unused).
 * PD2  - PIN2                         (unused).
 * PD3  - PIN3                         (unused).
 * PD4  - PIN4                         (unused).
 * PD5  - PIN5                         (unused).
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/*
 *  GPIOH setup:
 *
 * PH0  - PIN0                         (unused).
 * PH1  - PIN1                         (unused).
 * PH2  - PIN2                         (unused).
 * PH3  - PIN3                         (unused).
 * PH4  - PIN4                         (unused).
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
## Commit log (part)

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2017-02-15 Report ACFET status over CAN
2017-02-15 Change awake time to 2 mins
2017-02-15 Fix disabling battleshort from wakeup
2017-02-15 Fix reporting of pyro current and power
2017-02-16 some tweaks to m3fc state estimation and mission
2017-02-17 Add awake-time and low-power mode reporting
2017-02-17 Add bq40z60 reset command
2017-02-17 Change AOLD threshold with battleshort status
2017-02-17 Update m3psu parser for new messages
2017-02-21 create m3radio v2 from m3radio v1
2017-02-21 Chris' addition of low power mode
2017-02-21 latest blackmagic
2017-02-21 Track battleshort status in flight computer
2017-02-21 Add breakout r2 schematic and pcb
2017-02-22 Flight computer firmware changes no. 1
2017-02-22 PSU battleshorts added
2017-02-24 updated toad to new kicad
2017-02-27 Start designing new 5V DC/DC board
2017-02-27 bump agg-kicad
2017-02-28 Add note about temporary footprint
2017-02-28 Finish DCDC-5V schematic, first go at routing
2017-02-28 Fix expected datalen in battleshort handler
2017-02-28 Fixed PSU War Mode and tested
2017-02-28 Update with correct inductor footprint
2017-03-02 Update board with corrected XFL4020 footprint
2017-03-03 Change M3FC kalman filter to only do first order integrations
2017-03-04 Update JST-EH footprints on breakout board
2017-03-04 Update page settings on DCDC-5V board
2017-03-04 Schematic for DCDC-3V and routing progress
2017-03-04 Finish routing DCDC-3V
2017-03-05 Minor routing optimisation
2017-03-06 added battery temp
2017-03-07 Begin TDOA modifications
2017-03-07 added clock buffer
2017-03-08 updated agg-kicad
2017-03-08 Add todo list to schematic
2017-03-08 Remove unnecessary ADP3335
2017-03-08 Tidy up schematic, connect logic gates
2017-03-12 Drop Flask and use aiohttp instead
2017-03-12 Update example logfile
2017-03-14 pretend rocket data generator
2017-03-14 remove beeper-off line from m3fc
2017-03-14 refactor m3flash out of m3fc
2017-03-14 Add m3fc parser
2017-03-14 Fix m3dl overall status string
2017-03-16 Add m3radio parser
2017-03-16 Add m3ground parser
2017-03-16 Finish m3imu parser
2017-03-16 Add status parsing to m3psu parser
2017-03-23 Finish schematic, begin routing
2017-03-25 Revise component placement
2017-03-26 Everthing seems to fit onto pcb, begin routing
2017-03-26 Finish routing
2017-03-26 Actually connect gps pps to tim2
2017-03-28 completed toad psu
2017-03-29 Completed STM32 section
2017-03-29 Updated BOM and ERC
2017-04-01 make m3fc not beep continuously until armed...
2017-04-03 update for repaired avionics boards
2017-04-08 Ready to begin PCB
2017-04-08 started pcb
2017-04-10 added initial board layout
2017-04-12 First attempt at implementing trilateration algorithm in matlab
2017-04-13 Slightly optimise algorithm by removing for loops and cell array
2017-04-14 Further PCB progress
2017-04-29 pcb work
2017-05-14 Reduce imu board diameter
2017-05-14 Reduce radio board diameter
2017-05-16 moved Radio nSel to PA3 e.g. TIM2
2017-05-17 Begin increasing edge clearance...
2017-05-17 All copper moved to within 0.2mm of board edge
2017-06-20 checked schematic
2017-06-20 pcb progress
2017-06-27 further pcb work, signal routing mostly complete
2017-06-28 finished all signal and power routing
2017-06-28 finished via stitching
2017-06-28 added toad logo
2017-06-28 finished silk
2017-06-29 pcb complete
2017-06-29 modified all via sizes to meet CCL spec
2017-06-30 added radio clock dividers
2017-06-30 generated full board.h and configured chibios settings and peripheral and dma settings
2017-07-05 Create toad_gcs branch and begin porting trilateration algorithm to python
2017-07-06 Update agg-kicad to latest version
2017-07-06 add first go at m3pyro constant current prototype
2017-07-07 Implement stage one of trilateration algorithm in python
2017-07-07 Remove debugging print statements and small syntax fixes
2017-07-09 Finish implementing trilateration algorithm in python
2017-07-09 Tidy up trilateration and raise error when no real solution for quadratic (no intersection point)
2017-07-10 Add optional hack to set z=0 if no intersection found
2017-07-10 Initial review finished
2017-07-10 Tidy speedy_trilat and begin (very) rough outline of python package based on m3gcs
2017-07-11 First draft of install instructions (might just implement quaternions from scratch if easier)
2017-07-12 Use different quaternion module with simpler dependencies
2017-07-13 start m3pyro r2
2017-07-15 Move state dictionary into ekf module, and tidy speedy_trilat for use in package
2017-07-15 Use class to describe state(s), begin to outline interaction between processes
2017-07-15 Forgot to remove speedy_trilat.py (renamed to state_estimator.py)
2017-07-16 added psu status to driver
2017-07-17 further m3pyro r2 routing
2017-07-17 Fix small syntax errors
2017-07-19 created new branch and modified psu.c
2017-07-19 modified psu.c
2017-07-19 Add Simon's ecef code
2017-07-20 silk, tidyup, etc
2017-07-20 LED labels, gerbers
2017-07-21 remove old m3radio_v1 directory
2017-07-21 change ground fills to 32-segment circles
2017-07-21 update m3radio to si4461 (higher power variant)
2017-07-21 remove old back side silk 'radio' and 'gps' labels
2017-07-21 add zip of toad gerbers for manufacture
2017-07-22 slight further tidyup of myp3yro
2017-07-23 Interrupts (Lizzi)
2017-07-23 Remove adis from imu board
2017-07-23 Fix component values
2017-07-24 Update NFET footprint on 5v board, add pull-downs
2017-07-24 Begin gps driver
2017-07-24 Update radio bom
2017-07-25 Tidy up RF section and generate gerbers for manufacture.
2017-07-25 Potential update to breakout board r2
2017-07-25 Amend SMPS output cap on m3pyro r2 to 22u
2017-07-25 Add additional decoupling capacitor to 5V board
2017-07-26 Add logo to 3V board
2017-07-26 finalised bom
2017-07-26 Use updated LTC2975 footprint with better EP apertures
2017-07-27 Complete BOM for DCDC-5V board
2017-07-27 Add zipfile of m3pyro r2 gerbers
2017-07-27 Complete BOM for DCDC-3V board
2017-07-27 Begin imu pcb v3: add two more connectors, remove CAN resistor and jtag crossover
2017-07-27 move base pcb to top level
2017-07-28 Add new m3top board
2017-07-29 Finish imu v3, regenerate bom and stickers
2017-07-29 gerbers for m3imu r2
2017-07-31 modify m3radio fw to just constantly tx
2017-08-06 started timing driver
2017-08-06 Progress with gps driver, not yet compiled
2017-08-08 m3top bom
2017-08-08 m3pyro r2 bom
2017-08-08 updated BOM
2017-08-11 added temp comment
2017-08-11 Set up gps init function separate from gps thread
2017-08-11 added comments
2017-08-11 cs2100 half working
2017-08-12 Start on ltc2975 driver
2017-08-12 added Diya's status thread
2017-08-12 moved status LED update into its own function
2017-08-13 psu measurements working
2017-08-13 More DCDC driver work
2017-08-15 added activity state mods
2017-08-15 Update ublox state machine for TOAD
2017-08-18 fixed ack issues
2017-08-19 timer driver working and good progress made on measurement thread
2017-08-20 tested gps and added comments
2017-08-20 modified main.c
2017-08-20 Disable posecef messages and increase gps reset delay
2017-08-22 Updated with copyright declaration
    Copyright declaration's aern't necessarily required but are good communications practice
2017-08-22 added c
2017-08-23 Restructure gps setup and add posecef case to state machine
2017-08-23 Wait for nmea to stop, then clear the buffer before sending ubx
2017-08-26 Integrate new DCDC drivers with PSU firmware
2017-08-26 fixed all of gregs silly silly errors, the gps is now amazing and works
2017-08-26 Remove mailboxes from gps.c, set 1Hz pps to always on
2017-08-26 Set VIN range
2017-08-26 sr tx works, rx is not great
2017-08-26 gps not working again...
2017-08-27 add stencils and panel for batch 2 manufacturing
2017-08-27 latest agg-kicad
2017-08-27 new firmware for m3pyro r2
2017-08-27 acking fine
2017-08-27 gps working
2017-08-27 semaphores working ish
2017-08-27 add new stm32 ids
2017-08-27 started primary radio stuff
2017-08-27 sr and pr functioning well
2017-08-28 m3pyro r2 fw working, except for poor continuity resolution
2017-08-28 don't fire if not armed
2017-08-28 Fix pmbus L16 decoding to correctly read VOUT
2017-08-28 Update GCS PSU channel numbering
2017-08-28 Add new PSU MCUs to jtag_scan registry
2017-08-28 Begin updating GPS driver for m3radiov2
2017-08-29 Update chibios config for m3radio_v2
2017-08-29 wrote log file parser
2017-08-29 Add list of issues with pcb_r2
2017-08-29 psu logging fine and added units to parser
2017-08-30 added log_telem and some comments
2017-08-30 last commit before moving to events
2017-08-30 Work on m3radio firmware for TOAD
2017-08-30 Fix compile errors this time
2017-08-31 havent broken anything yet
2017-08-31 core slave functionality written
2017-08-31 need to change usb pins
2017-08-31 usb init works
2017-09-01 usb serial vomit thread complete
2017-09-01 Fix various bugs including lack of external i2c pullups
2017-09-01 updated log file parser
2017-09-01 fixed bug in log lab stats
2017-09-01 first telemetry test working
2017-09-01 Manually add labrador in shared/
2017-09-01 Fix bugs and use pps to signal radio tx
2017-09-01 started master fw
2017-09-01 Fix readme typo
2017-09-02 added master sr functionality, logging and parsing of rx packets
2017-09-03 Begin pyqt gui
2017-09-03 added sc card config
2017-09-03 removed debug statements
2017-09-03 More gcs work
2017-09-03 Gui work and reorganise directory
2017-09-03 Add .gitignore
2017-09-04 Fix .gitignore
2017-09-04 Further GUI work
2017-09-05 More GUI work
2017-09-06 Remove debug stuff, gui ready for initial testing
2017-09-06 Separate USB stats from toad stats
2017-09-06 Add connect button
2017-09-07 Fix sr_rx packet payload length
2017-09-07 Add ENU conversion
2017-09-09 First attempt at running time of flight ranging packets through trilat algorithm
2017-09-09 Print packets to terminal (untested)
2017-09-11 started kml stuff
2017-09-11 add new m3fc id to registry
2017-09-12 HTML map attempt 1
2017-09-13 Fix CAN message indices in m3psu
2017-09-13 Update m3psu parser to handle new DCDC boards
2017-09-14 Fix mutex scope in smbus driver to prevent reentrant access causing corruption
2017-09-14 Assorted gui work
2017-09-16 Finish testing code, trilat appears to work but pyqt evaluatejavascript is slow and causes gui to freeze
2017-09-16 Update GUI todo list
2017-09-17 M3Radio FW TX at exactly top of second
2017-09-18 more reliable radio gc
2017-09-18 use mempool for lab01gc usb tx thd
2017-09-19 start updating m3fc config script
2017-09-19 todo list...
2017-09-19 don't process accel values that are out of range
2017-09-19 prototype m3pyro resistance measurement
2017-09-19 update todo
2017-09-20 fix fc se bug
2017-09-20 update gcs for new m3fc pyro, and fix heading height
2017-09-20 improve resistance measurement
2017-09-20 remove debug print statement from gcs pyro
2017-09-21 fix gcs status bug
2017-09-21 don't send git version on radio so often
2017-09-21 Add m3psu awake_time message to m3radio router
2017-09-21 Add start of new React gcs frontend
2017-09-21 new core.yaml scale/offset
2017-09-22 Work on integrating new gcs frontend
2017-09-22 some new config settings, still waiting final profile
2017-09-22 import latest toad_gcs from greg's usb
2017-09-22 Add version parsing
2017-09-22 Integrate frontend into gcs backend
2017-09-23 Add last heard times to data points
2017-09-23 Fix compiler warnings in parsers
2017-09-23 Add buttons to gcs
2017-09-23 final toad tweaks
2017-10-06 added plain text logs
2017-10-06 Add commands, host with Flask
2017-10-06 Minor tweaks
2017-10-06 Initial attempt at trilateration using TOAD logs
2017-10-06 Process unfilled bins once logfiles have been read
2017-10-07 Commit output from 'from_logfile.py'
2017-10-07 Hardcode TOAD positions
2017-10-07 Display sorted ref points in text file
